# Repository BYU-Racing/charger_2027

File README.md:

# 👋 Hey Rowan — Welcome to Markdown!

> This file is a tour of what Markdown can do. Open it in a viewer that renders Markdown
> (GitHub, VS Code preview, Obsidian, Typora, etc.) to see it in its full glory.
> Then open it as plain text to see how simple the source is.

---

## 📑 Table of Contents

1. [Headings](#-headings)
2. [Text Formatting](#-text-formatting)
3. [Lists](#-lists)
4. [Links](#-links)
5. [Images](#-images)
6. [Tables](#-tables)
7. [Code](#-code)
8. [Blockquotes & Callouts](#-blockquotes--callouts)
9. [Fancy Extras](#-fancy-extras)
10. [Diagrams & Math](#-diagrams--math)

---

## 🔠 Headings

# Heading 1
## Heading 2
### Heading 3
#### Heading 4
##### Heading 5
###### Heading 6

Alternate syntax for the big two:

Heading 1, underline style
==========================

Heading 2, underline style
--------------------------

---

## ✍️ Text Formatting

| What you type | What you get |
|---|---|
| `*italic*` or `_italic_` | *italic* |
| `**bold**` or `__bold__` | **bold** |
| `***bold italic***` | ***bold italic*** |
| `~~strikethrough~~` | ~~strikethrough~~ |
| `` `inline code` `` | `inline code` |
| `<kbd>Ctrl</kbd> + <kbd>C</kbd>` | <kbd>Ctrl</kbd> + <kbd>C</kbd> |
| `H<sub>2</sub>O` | H<sub>2</sub>O |
| `E = mc<sup>2</sup>` | E = mc<sup>2</sup> |
| `<mark>highlight</mark>` | <mark>highlight</mark> |

End a line with two spaces (or a backslash)\
to force a line break without starting a new paragraph.

Need a literal asterisk? Escape it: \*not italic\*, \# not a heading, \`not code\`.

---

## 📋 Lists

### Unordered
- Coffee ☕
- Tea 🍵
  - Green
  - Black
    - Earl Grey
    - English Breakfast
- Hot chocolate 🍫

### Ordered
1. Wake up
2. Read this file
3. Become a Markdown wizard 🧙
   1. Practice tables
   2. Show off to friends

> Fun fact: the actual numbers don't matter — `1. 1. 1.` still renders as 1, 2, 3.

### Task list (checkboxes)
- [x] Learn headings
- [x] Learn bold and italic
- [ ] Make a table from scratch
- [ ] Write a README for a project

---

## 🔗 Links

- Inline link: [CommonMark spec](https://commonmark.org)
- Link with a hover title: [Markdown Guide](https://www.markdownguide.org "The friendliest Markdown reference")
- Bare autolink: <https://github.github.com/gfm/>
- Reference-style link: the original [Markdown project][gruber] by John Gruber.
- Jump within this doc: [back to the top](#-hey-rowan--welcome-to-markdown)

[gruber]: https://daringfireball.net/projects/markdown/

---

## 🖼️ Images

A basic image:

An image that's also a link (click it!):

A custom placeholder image with text baked in:

Resized & centered using a bit of HTML (works on GitHub and most viewers):

---

## 📊 Tables

### Basic table with column alignment

| Left-aligned | Centered | Right-aligned |
|:-------------|:--------:|--------------:|
| apples       | 🍎       | $1.20         |
| bananas      | 🍌       | $0.50         |
| cherries     | 🍒       | $4.75         |
| **Total**    |          | **$6.45**     |

### Comparison table

| Feature            | Plain text | Markdown | Word doc |
|--------------------|:----------:|:--------:|:--------:|
| Easy to write      | ✅         | ✅       | ⚠️       |
| Looks nice         | ❌         | ✅       | ✅       |
| Works in Git       | ✅         | ✅       | ❌       |
| Readable as source | ✅         | ✅       | ❌       |

> Tip: the pipes don't need to line up perfectly — Markdown is forgiving. Lining them up just makes the source prettier.

---

## 💻 Code

Inline: run `npm install` to get started.

A fenced code block with syntax highlighting:

```python
def greet(name: str) -> str:
    """Say hi to a friend."""
    return f"Hello, {name}! Welcome to Markdown. 🎉"

print(greet("Rowan"))
```

```javascript
const skills = ["headings", "tables", "images"];
skills.forEach((s) => console.log(`Rowan learned ${s}!`));
```

```bash
# Shell commands look great too
echo "Markdown is awesome" > notes.md
cat notes.md
```

```diff
- old boring plain text
+ shiny new formatted Markdown
```

```json
{
  "name": "Rowan",
  "markdownLevel": "expert",
  "favoriteFeature": "tables"
}
```

---

## 💬 Blockquotes & Callouts

> A plain blockquote.
>
> > And a nested one inside it.
>
> — Someone wise

GitHub-style alerts (render as colored callouts on GitHub):

> [!NOTE]
> Useful information that users should know.

> [!TIP]
> Use `Ctrl + Shift + V` in VS Code to preview Markdown.

> [!IMPORTANT]
> Key information users need to know.

> [!WARNING]
> Markdown can be addictive.

> [!CAUTION]
> Once you learn tables you'll never go back.

---

## ✨ Fancy Extras

### Collapsible section

<details>
<summary>🎁 Click to reveal a surprise</summary>

You found it! Collapsible sections are great for long logs, spoilers, or FAQs.

- They can contain **any** Markdown
- Even lists and code:

```text
¯\_(ツ)_/¯
```

</details>

### Footnotes

Markdown was created in 2004[^1] and is now used basically everywhere[^2].

[^1]: By John Gruber, with help from Aaron Swartz.
[^2]: README files, chat apps, note-taking apps, documentation sites, and more.

### Emoji shortcodes (GitHub, Slack, Discord)

:rocket: :tada: :sparkles: :coffee: :books:

### Horizontal rules

Three or more dashes, asterisks, or underscores:

***

___

---

## 📈 Diagrams & Math

### Mermaid diagram (renders on GitHub, Obsidian, many others)

```mermaid
flowchart LR
    A[Write plain text] --> B{Add Markdown syntax}
    B --> C[Headings]
    B --> D[Tables]
    B --> E[Images]
    C & D & E --> F[✨ Beautiful document ✨]
```

```mermaid
pie title How Rowan spends time
    "Writing Markdown" : 45
    "Admiring tables" : 30
    "Snacks" : 25
```

### Math (LaTeX, supported on GitHub & Obsidian)

Inline math: $E = mc^2$

Block math:

$$
\sum_{n=1}^{\infty} \frac{1}{n^2} = \frac{\pi^2}{6}
$$

---

## 📚 Keep Learning

- [Markdown Guide — Basic Syntax](https://www.markdownguide.org/basic-syntax/)
- [Markdown Guide — Extended Syntax](https://www.markdownguide.org/extended-syntax/)
- [GitHub Flavored Markdown Spec](https://github.github.com/gfm/)
- [CommonMark Interactive Tutorial](https://commonmark.org/help/tutorial/)

<p align="center"><sub>Made with ❤️ and a lot of <code>#</code> symbols — happy writing, Rowan!</sub></p>

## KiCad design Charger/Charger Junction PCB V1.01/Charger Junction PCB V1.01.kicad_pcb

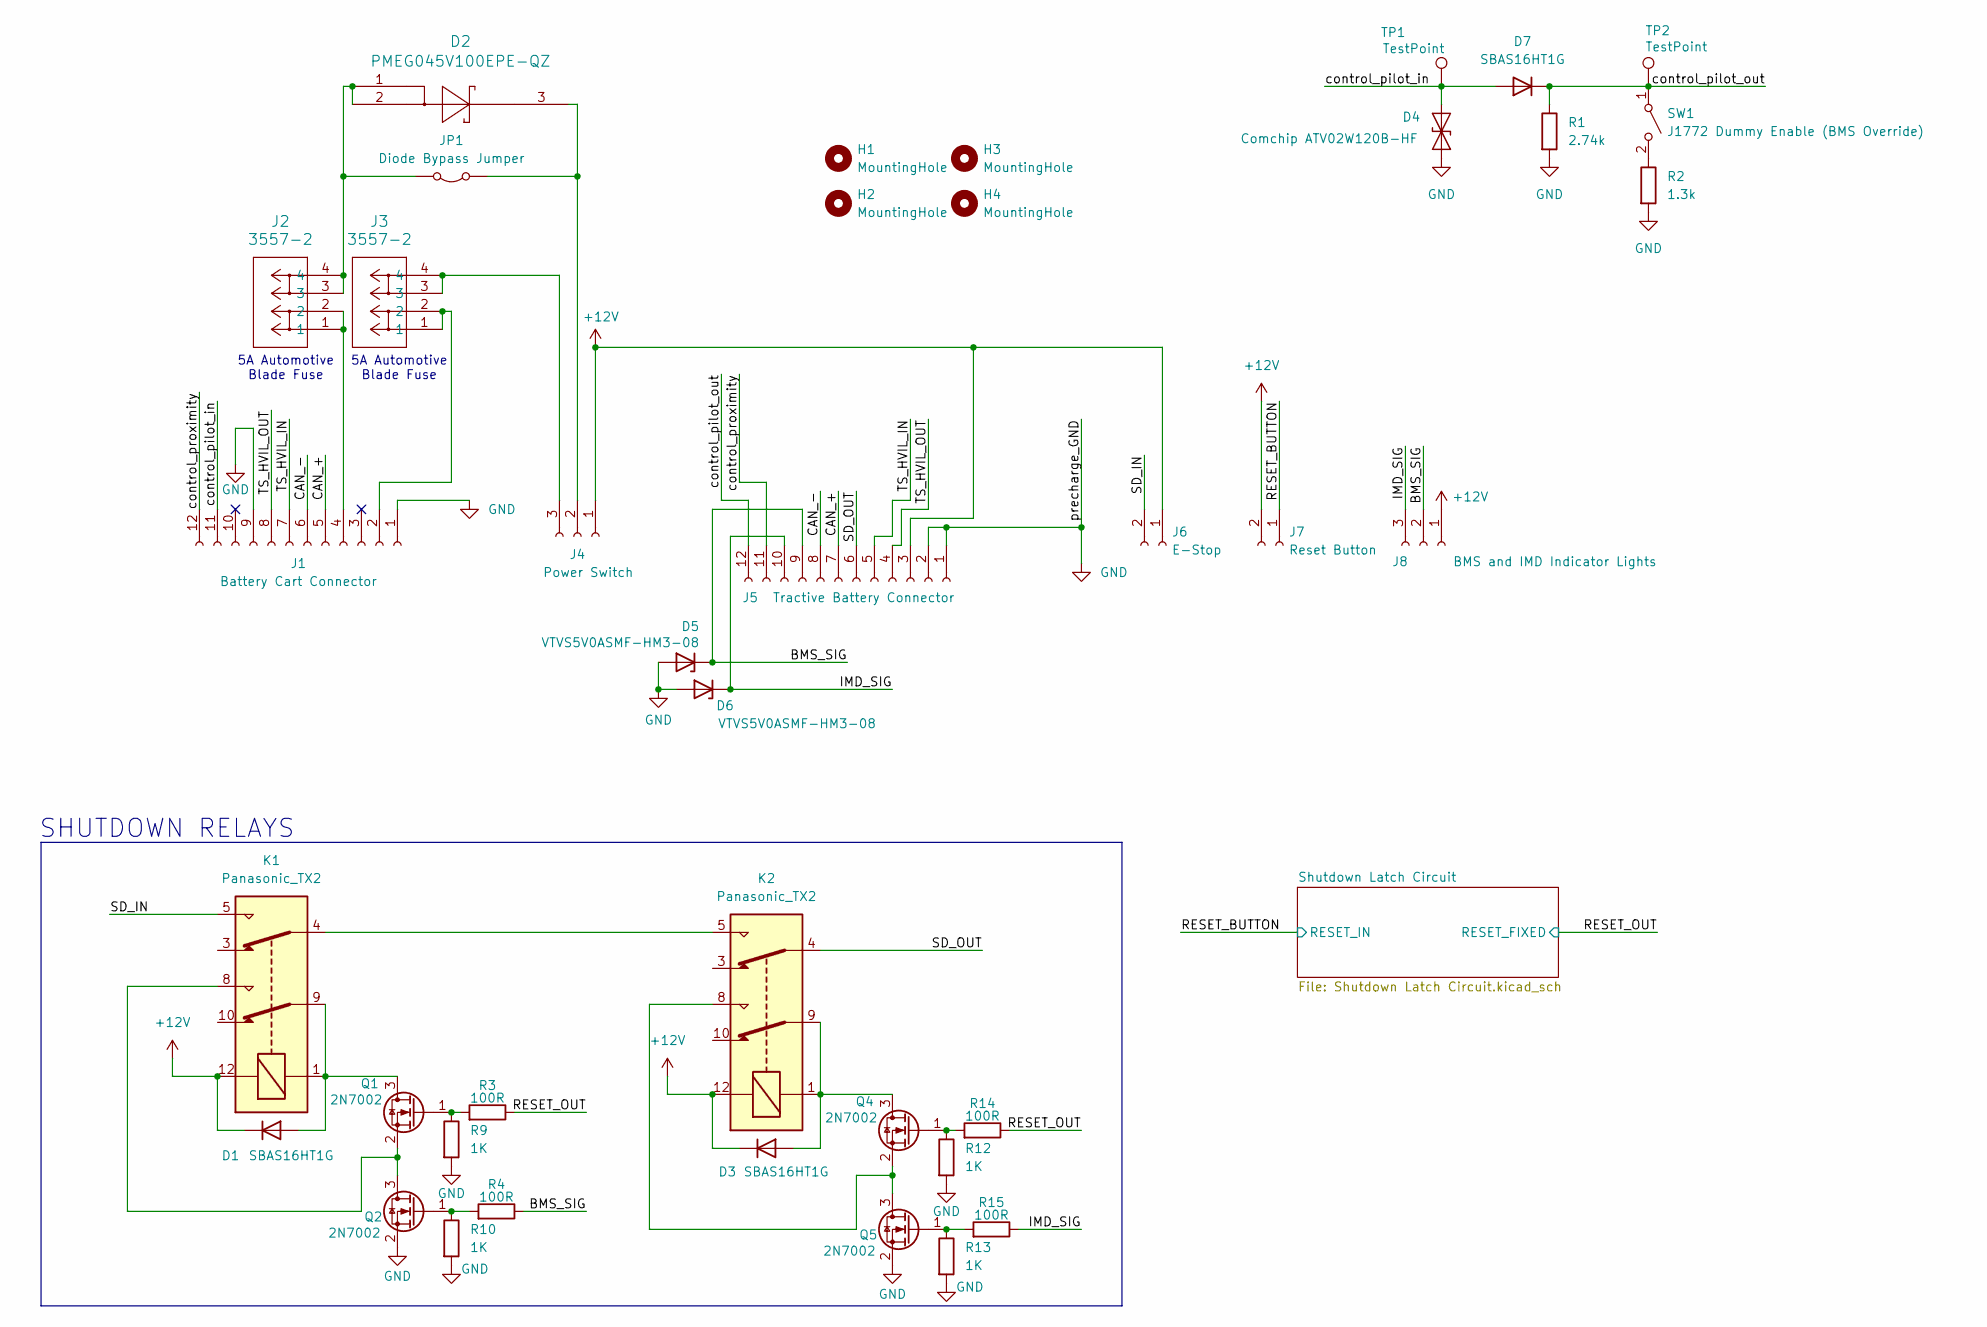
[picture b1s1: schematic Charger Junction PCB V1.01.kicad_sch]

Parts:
D1, D3, D7: SBAS16HT1G; D_SOD-323_HandSoldering
D2: PMEG045V100EPE-QZ; SOT1289_CFP15_NEX
D4: Comchip ATV02W120B-HF; D_SOD-123F
D5, D6: VTVS5V0ASMF-HM3-08; D_SMF
H1, H2, H3, H4: MountingHole; MountingHole_3.2mm_M3
J1: Battery Cart Connector; DT13-12
J2, J3: 3557-2; CONN_3557-2_KEY
J4: Power Switch; CONN_SD-43650-006_03_MOL
J5: Tractive Battery Connector; DT13-12
J6: E-Stop; CONN_SD-43650-006_02_MOL
J7: Reset Button; CONN_SD-43650-006_02_MOL
J8: BMS and IMD Indicator Lights; CONN_SD-43650-006_03_MOL
JP1: Diode Bypass Jumper; SolderJumper-2_P_5A_6.0x4.0mm
K1, K2: Panasonic_TX2; Relay_DPDT_Panasonic_TXSA
Q1, Q2, Q4, Q5: 2N7002; SOT-23
R1: 2.74k; R_0805_2012Metric_Pad1.20x1.40mm_HandSolder
R2: 1.3k; R_0805_2012Metric_Pad1.20x1.40mm_HandSolder
R3, R4, R14, R15: 100R; R_0805_2012Metric_Pad1.20x1.40mm_HandSolder
R9, R10, R12, R13: 1K; R_0805_2012Metric_Pad1.20x1.40mm_HandSolder
SW1: J1772 Dummy Enable (BMS Override); SPST_ELC_shop_switch_10x16mm
TP1, TP2: TestPoint; TestPoint_Loop_D2.54mm_Drill1.5mm_Beaded

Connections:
+12V: D1.1 (K), D3.1 (K), J4.1, J5.3, J6.1, J7.2, J8.1, K1.12, K2.12; also elsewhere on the board
/BMS_SIG: D5.1 (K), J5.9, J8.2, R4.1
/CAN_+: J1.5, J5.7
/CAN_-: J1.6, J5.8
/IMD_SIG: D6.1 (K), J5.10, J8.3, R15.1
/RESET_BUTTON: J7.1; also elsewhere on the board
/RESET_OUT: R3.1, R14.1; also elsewhere on the board
/SD_IN: J6.2, K1.5
/SD_OUT: J5.6, K2.4
/TS_HVIL_IN: J1.7, J5.5
/TS_HVIL_OUT: J1.8, J5.4
/control_pilot_in: D4.2 (A2), D7.2 (A), J1.11, TP1.1 (1_1)
/control_pilot_out: D7.1 (K), J5.12, R1.1, SW1.1 (A), TP2.1 (1_1)
/control_proximity: J1.12, J5.11
GND: D4.1 (A1), D5.2 (A), D6.2 (A), J1.1, J1.9, J5.1, J5.2, Q2.2 (S), Q5.2 (S), R1.2, R2.2, R9.2, R10.2, R12.2, R13.2; also elsewhere on the board
unnamed: D1.2 (A), K1.1, K1.9, Q1.3 (D)
unnamed: D3.2 (A), K2.1, K2.9, Q4.3 (D)
unnamed: J1.2, J3.1, J3.2
unnamed: J1.4, J2.1, J2.2
unnamed: D2.3, J4.2, JP1.1 (A)
unnamed: J3.3, J3.4, J4.3
unnamed: D2.1, D2.2, J2.3, J2.4, JP1.2 (B)
unnamed: K1.4, K2.5
unnamed: Q1.1 (G), R3.2, R9.1
unnamed: K1.8, Q1.2 (S), Q2.3 (D)
unnamed: Q2.1 (G), R4.2, R10.1
unnamed: Q4.1 (G), R12.1, R14.2
unnamed: K2.8, Q4.2 (S), Q5.3 (D)
unnamed: Q5.1 (G), R13.1, R15.2
unnamed: R2.1, SW1.2 (B)

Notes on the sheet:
5A Automotive Blade Fuse
SHUTDOWN RELAYS

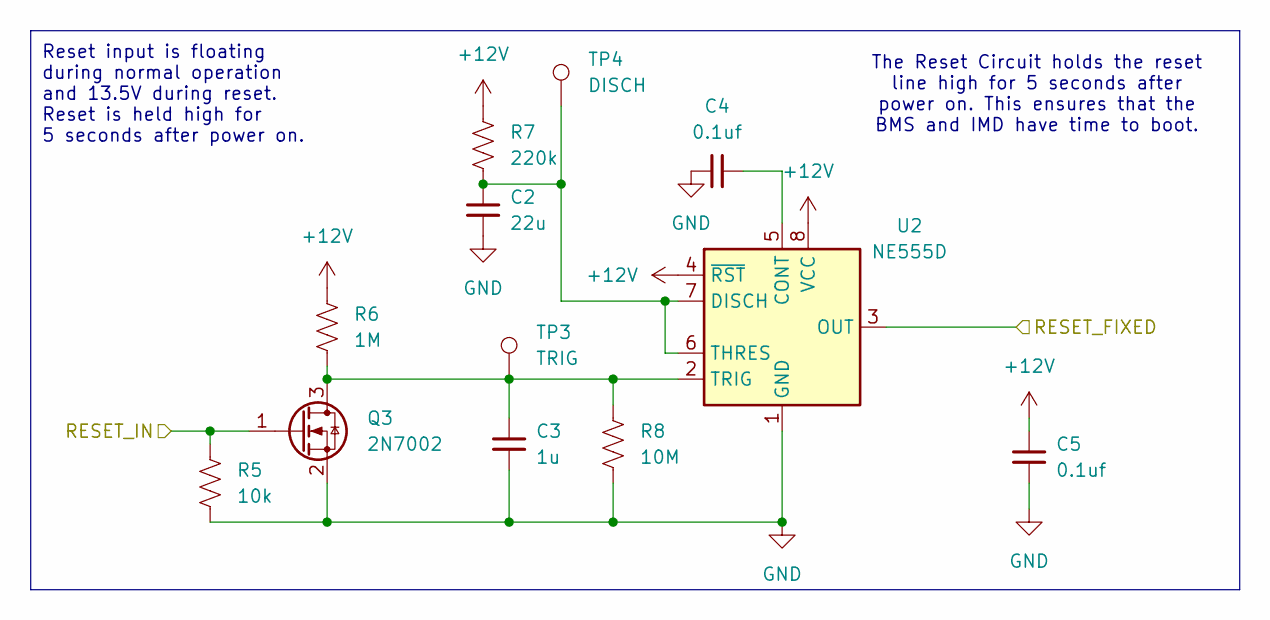
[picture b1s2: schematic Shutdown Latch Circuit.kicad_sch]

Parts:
C2: 22u; C_0805_2012Metric_Pad1.18x1.45mm_HandSolder
C3: 1u; C_0805_2012Metric_Pad1.18x1.45mm_HandSolder
C4, C5: 0.1uf; C_0805_2012Metric_Pad1.18x1.45mm_HandSolder
Q3: 2N7002; SOT-23
R5: 10k; R_0805_2012Metric_Pad1.20x1.40mm_HandSolder
R6: 1M; R_0805_2012Metric_Pad1.20x1.40mm_HandSolder
R7: 220k; R_0805_2012Metric_Pad1.20x1.40mm_HandSolder
R8: 10M; R_0805_2012Metric_Pad1.20x1.40mm_HandSolder
TP3: TRIG; TestPoint_Loop_D2.54mm_Drill1.5mm_Beaded
TP4: DISCH; TestPoint_Loop_D2.54mm_Drill1.5mm_Beaded
U2: NE555D; SOIC-8_3.9x4.9mm_P1.27mm; Operating Voltage (V) 12; MPN TLC555QDRQ1

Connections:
+12V: C5.1, R6.2, R7.2, U2.4 (~RST), U2.8 (VCC); also elsewhere on the board
/RESET_BUTTON: Q3.1 (G), R5.2; also elsewhere on the board
/RESET_OUT: U2.3 (OUT); also elsewhere on the board
GND: C2.1, C3.1, C4.1, C5.2, Q3.2 (S), R5.1, R8.1, U2.1 (GND); also elsewhere on the board
unnamed: C3.2, Q3.3 (D), R6.1, R8.2, TP3.1 (1_1), U2.2 (TRIG)
unnamed: C4.2, U2.5 (CONT)
unnamed: C2.2, R7.1, TP4.1 (1_1), U2.6 (THRES), U2.7 (DISCH)

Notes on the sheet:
Reset input is floating during normal operation and 13.5V during reset. Reset is held high for 5 seconds after power on.
The Reset Circuit holds the reset line high for 5 seconds after power on. This ensures that the BMS and IMD have time to boot.

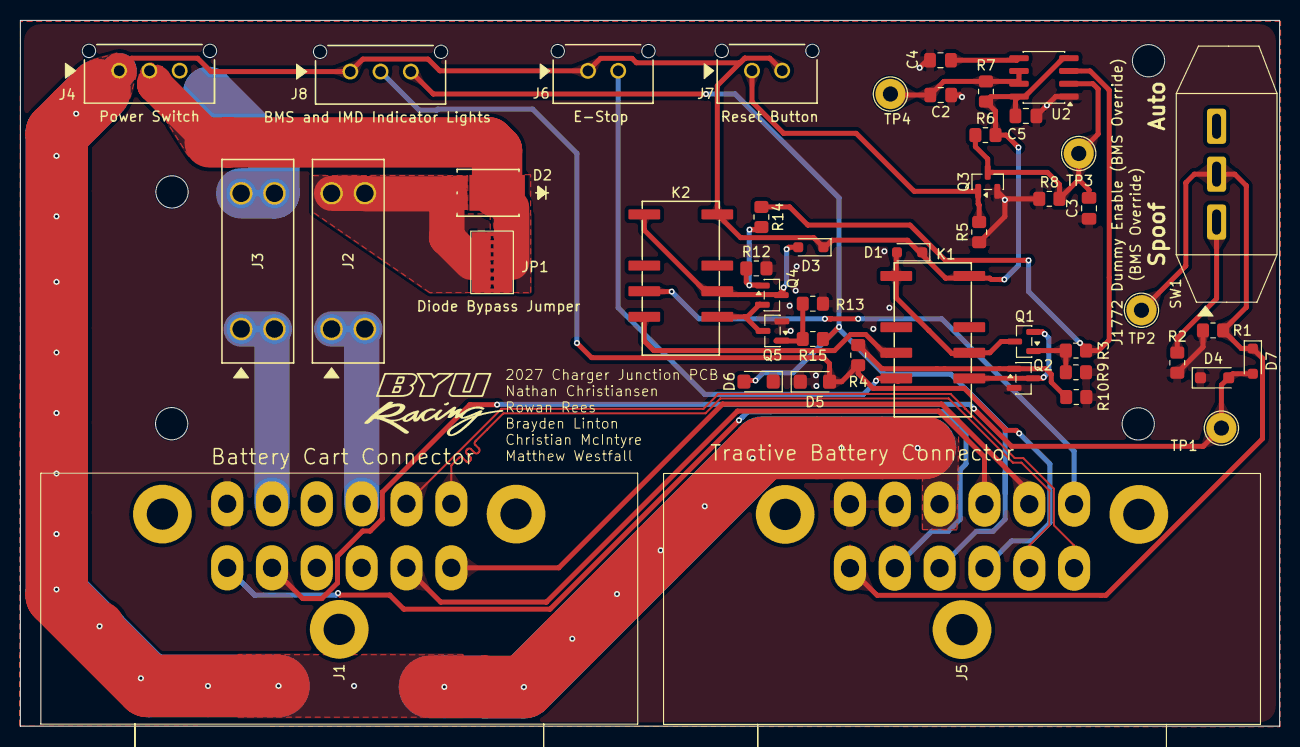
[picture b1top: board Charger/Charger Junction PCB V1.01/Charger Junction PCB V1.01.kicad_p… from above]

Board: 2 copper layers, 124.9 x 70.0 mm, 51 parts (0 on the bottom side), 33 nets.

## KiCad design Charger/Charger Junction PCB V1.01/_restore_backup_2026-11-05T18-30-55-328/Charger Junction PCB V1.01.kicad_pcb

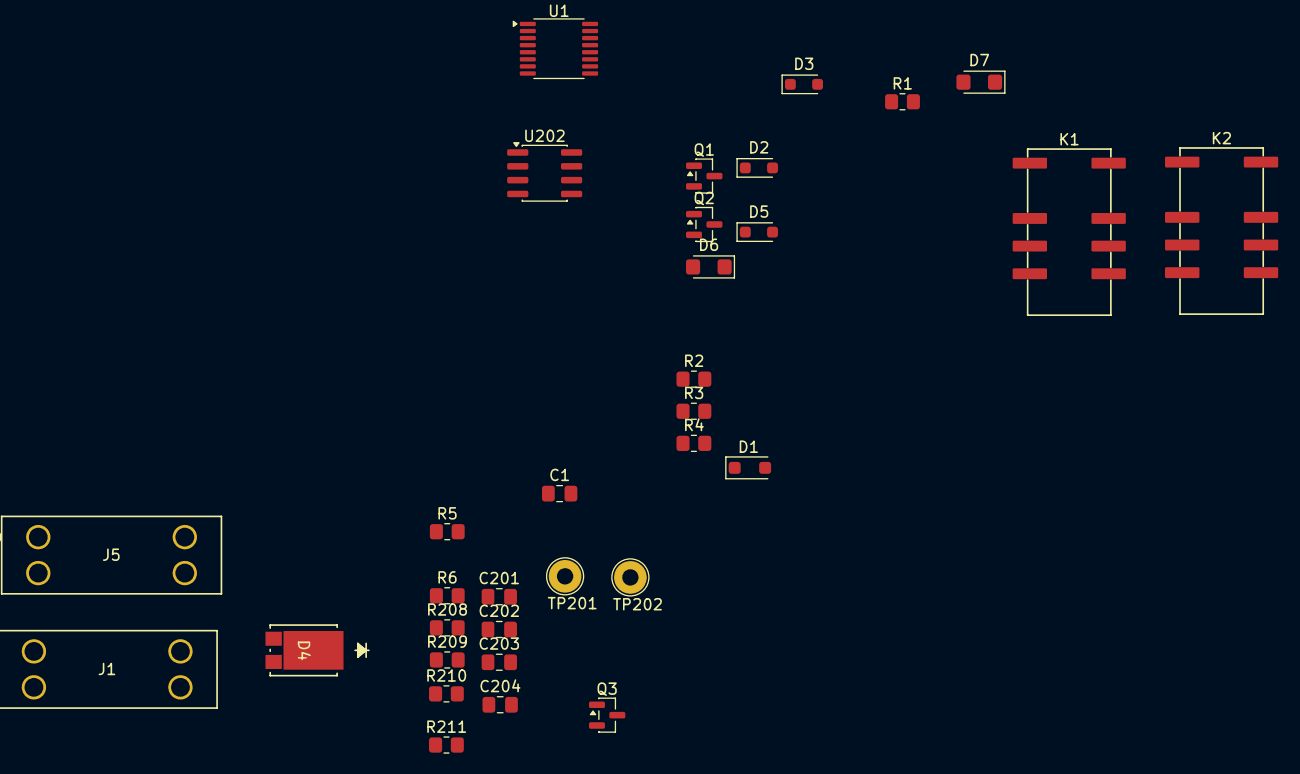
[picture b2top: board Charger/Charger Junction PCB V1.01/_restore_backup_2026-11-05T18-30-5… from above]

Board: 2 copper layers, 33 parts (0 on the bottom side), 22 nets, no tracks yet.

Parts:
C1: 100nf; C_0805_2012Metric_Pad1.18x1.45mm_HandSolder
C201: 22u; C_0805_2012Metric_Pad1.18x1.45mm_HandSolder
C202: 1u; C_0805_2012Metric_Pad1.18x1.45mm_HandSolder
C203: 0.1u; C_0805_2012Metric_Pad1.18x1.45mm_HandSolder
C204: 100n; C_0805_2012Metric_Pad1.18x1.45mm_HandSolder
D1: Comchip ATV02W120B-HF; D_SOD-123F
D2, D3, D5: SBAS16HT1G; D_SOD-323_HandSoldering
D4: PMEG045V100EPE-QZ; SOT1289_CFP15_NEX
D6, D7: VTVS5V0ASMF-HM3-08; D_SMF
J1, J5: 3557-2; CONN_3557-2_KEY
K1, K2: Panasonic_TX2; Relay_DPDT_Panasonic_TXSA
Q1, Q2, Q3: 2N7002; SOT-23
R1: 2.74k; R_0805_2012Metric_Pad1.20x1.40mm_HandSolder
R2: 1.3k; R_0805_2012Metric_Pad1.20x1.40mm_HandSolder
R3, R4: 100R; R_0805_2012Metric_Pad1.20x1.40mm_HandSolder
R5, R6, R208: 10k; R_0805_2012Metric_Pad1.20x1.40mm_HandSolder
R209: 1M; R_0805_2012Metric_Pad1.20x1.40mm_HandSolder
R210: 220k; R_0805_2012Metric_Pad1.20x1.40mm_HandSolder
R211: 10M; R_0805_2012Metric_Pad1.20x1.40mm_HandSolder
TP201: TRIG; TestPoint_Loop_D2.54mm_Drill1.5mm_Beaded
TP202: DISCH; TestPoint_Loop_D2.54mm_Drill1.5mm_Beaded
U1: CD4043B; TSSOP-16_4.4x5mm_P0.65mm
U202: NE555D; SOIC-8_3.9x4.9mm_P1.27mm

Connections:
+12V: C1.1, C204.1, K1.12, K2.12, R209.2, R210.2, U1.5 (ENABLE), U1.16 (VDD), U202.4 (~RST), U202.8 (VCC)
/BMS_SIG: D2.1 (K), K1.1, Q1.3 (D)
/IMD_SIG: D5.1 (K), K2.1, Q2.3 (D)
/RESET_BUTTON: Q3.1 (G), R208.2
/Shutdown Latch Circuit/BMS_LATCHED: R3.1, U1.9
/Shutdown Latch Circuit/BMS_SD_STATUS: D6.1 (K), R6.1, U1.6
/Shutdown Latch Circuit/IMD_LATCHED: R4.1, U1.2
/Shutdown Latch Circuit/IMD_SD_STATUS: D7.1 (K), R5.1, U1.4
/Shutdown Latch Circuit/RESET_FIXED: U1.3, U1.7, U202.3 (OUT)
/control_pilot_in: D1.2 (A2), D3.2 (A)
/control_pilot_out: D3.1 (K), R1.1
GND: C1.2, C201.1, C202.1, C203.1, C204.2, D1.1 (A1), D2.2 (A), D5.2 (A), D6.2 (A), D7.2 (A), Q1.2 (S), Q2.2 (S), Q3.2 (S), R1.2, R2.2, R5.2, R6.2, R208.1, R211.1, U1.8 (VSS), U202.1 (GND)
unnamed: D4.1, D4.2, J1.3, J1.4
unnamed: J5.1, J5.2
unnamed: J1.1, J1.2
unnamed: J5.3, J5.4
unnamed: K1.9, K2.8
unnamed: Q1.1 (G), R3.2
unnamed: Q2.1 (G), R4.2
unnamed: C202.2, Q3.3 (D), R209.1, R211.2, TP201.1 (1_1), U202.2 (TRIG)
unnamed: C203.2, U202.5 (CONT)
unnamed: C201.2, R210.1, TP202.1 (1_1), U202.6 (THRES), U202.7 (DISCH)
